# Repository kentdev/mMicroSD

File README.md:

mMicroSD
========

Source code and EAGLE schematic for the mMicroSD peripheral for the M2 (http://medesign.seas.upenn.edu/index.php/Guides/MaEvArM), which allows it to read from and write to a microSD card.

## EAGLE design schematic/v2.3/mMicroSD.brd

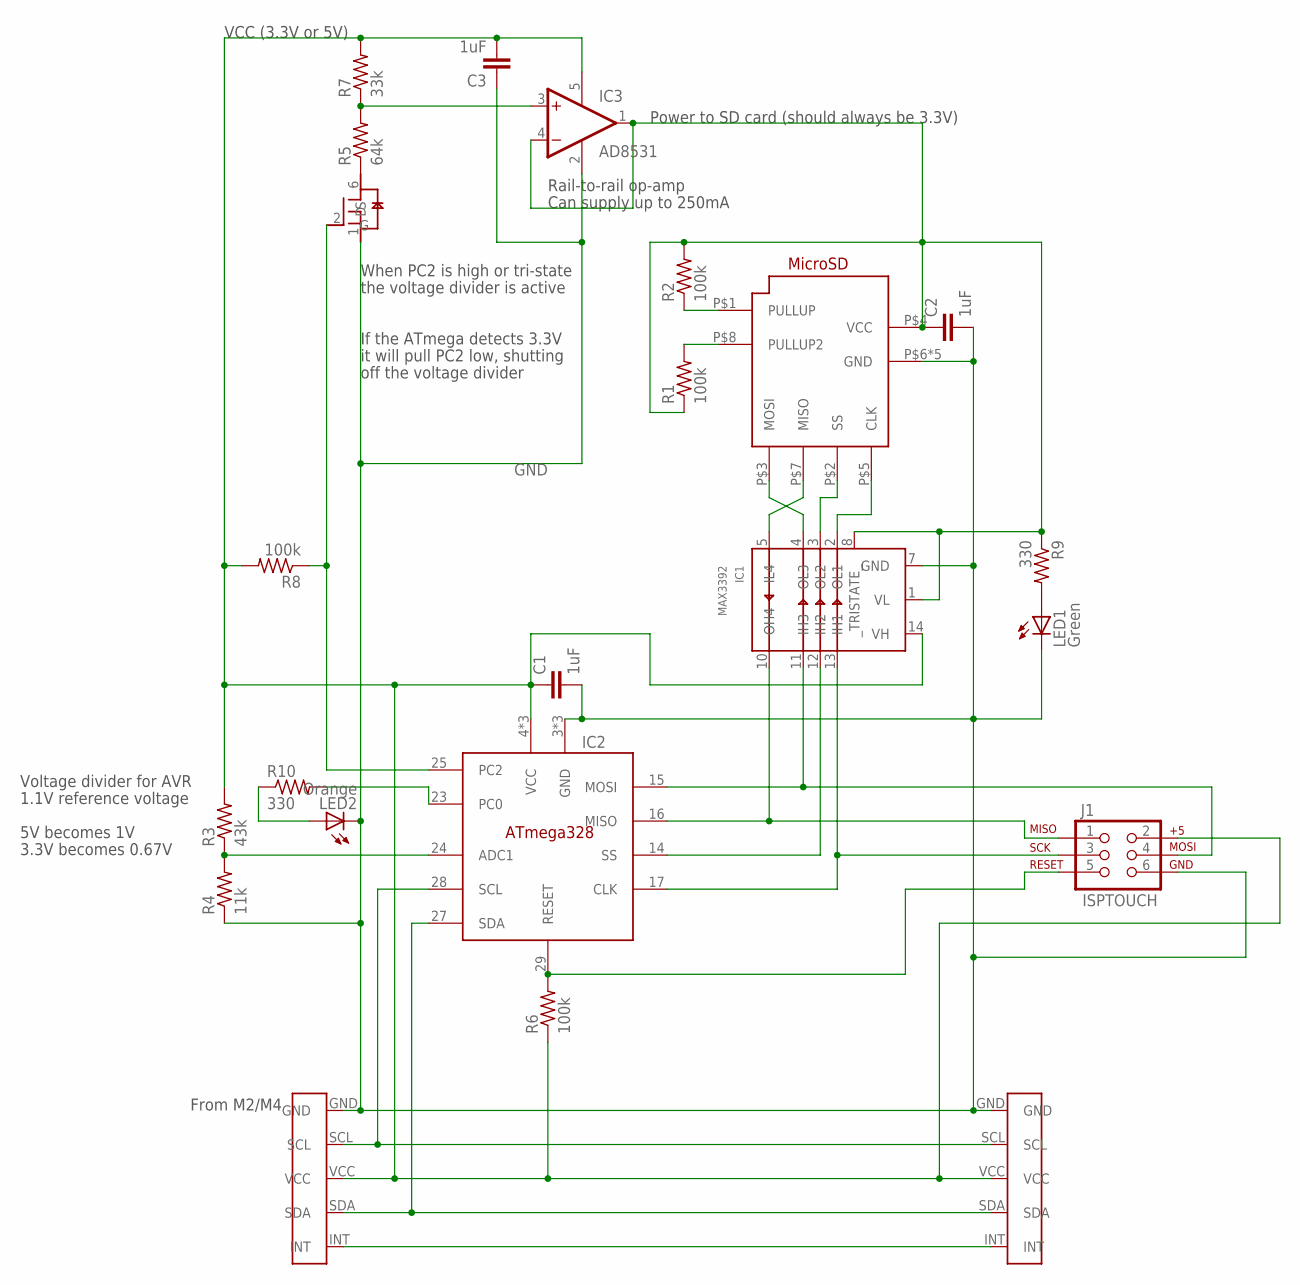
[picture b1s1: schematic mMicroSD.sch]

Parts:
C1, C2, C3: 1uF; C0603
IC1: MAX3392; 14-TSSOP
IC2: ATMEGA328
IC3: AD8531; SOT-23-5
J1: ISPTOUCH; AVX_9188_6-WAY_SMT
LED1: Green; SML0603
LED2: Orange; SML0603
M1: NTJD5121N; SOT-363
R1, R2, R6, R8: 100k; R0603
R3: 43k; R0603
R4: 11k; R0603
R5: 64k; R0603
R7: 33k; R0603
R9, R10: 330; R0603
SDCONN: 101-00660-68-6
U$1: MBUS_OUT
U$2: MBUS_IN

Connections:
ADC_LINE: IC2.24 (ADC1), R3.1, R4.2
DATA_LED: IC2.23 (PC0), R10.2
GATE: IC2.25 (PC2), M1.2 (G), R8.1
GND: C1.2, C2.2, C3.1, IC1.7 (GND), IC2.3 (GND), IC2.5 (GND), IC2.21 (GND), IC3.2 (V-), J1.6, LED1.C, LED2.C, M1.1 (S), R4.1, SDCONN.P$6 (GND), SDCONN.P$9 (GND), SDCONN.P$10 (GND), SDCONN.P$11 (GND), SDCONN.P$12 (GND), U$1.GND, U$2.GND
INT: U$1.INT, U$2.INT
MISO: IC1.10 (OH4), IC2.16 (MISO), J1.1
MOSI: IC1.11 (IH3), IC2.15 (MOSI), J1.4
unnamed: M1.6 (D), R5.1
unnamed: LED1.A, R9.2
unnamed: LED2.A, R10.1
unnamed: R1.2, SDCONN.P$8 (PULLUP2)
unnamed: R2.1, SDCONN.P$1 (PULLUP)
OPAMP_VOLTAGE: IC3.3 (+IN), R5.2, R7.1
RESET: IC2.29 (RESET), J1.5, R6.2
SCK: IC1.13 (IH1), IC2.17 (CLK), J1.3
SCL: IC2.28 (SCL), U$1.SCL, U$2.SCL
SDA: IC2.27 (SDA), U$1.SDA, U$2.SDA
SD_CS: IC1.3 (OL2), SDCONN.P$2 (SS)
SD_MISO: IC1.5 (IL4), SDCONN.P$7 (MISO)
SD_MOSI: IC1.4 (OL3), SDCONN.P$3 (MOSI)
SD_SCK: IC1.2 (OL1), SDCONN.P$5 (CLK)
SS: IC1.12 (IH2), IC2.14 (SS)
VCC_MBUS: C1.1, C3.2, IC1.14 (VH), IC2.4 (VCC), IC2.6 (VCC), IC2.18 (VCC), IC3.5 (V+), J1.2, R3.2, R6.1, R7.2, R8.2, U$1.VCC, U$2.VCC
VCC_SD: C2.1, IC1.1 (VL), IC1.8 (_TRISTATE_), IC3.1 (OUT), IC3.4 (-IN), R1.1, R2.2, R9.1, SDCONN.P$4 (VCC)

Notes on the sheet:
From M2/M4
VCC (3.3V or 5V)
Voltage divider for AVR
1.1V reference voltage
5V becomes 1V
3.3V becomes 0.67V
When PC2 is high or tri-state
the voltage divider is active
If the ATmega detects 3.3V
it will pull PC2 low, shutting
off the voltage divider
Power to SD card (should always be 3.3V)
Rail-to-rail op-amp
Can supply up to 250mA

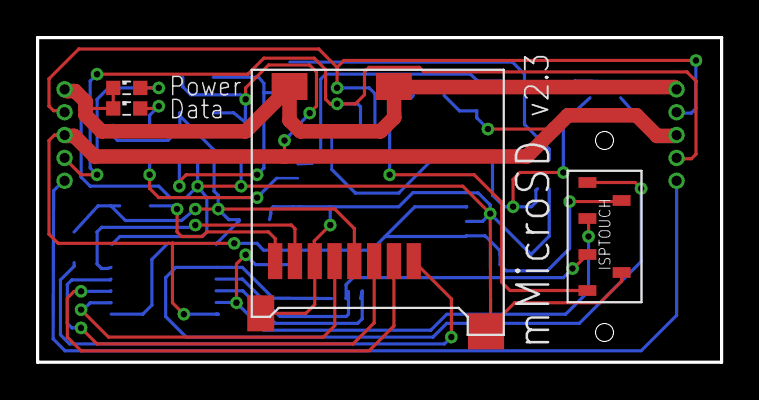
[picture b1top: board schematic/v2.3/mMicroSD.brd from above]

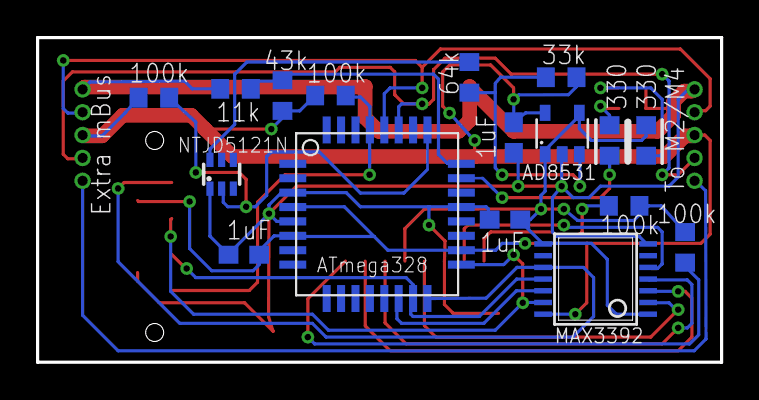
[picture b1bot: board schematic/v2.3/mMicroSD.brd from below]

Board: 2 copper layers, 38.0 x 18.0 mm, 23 parts (17 on the bottom side), 24 nets.

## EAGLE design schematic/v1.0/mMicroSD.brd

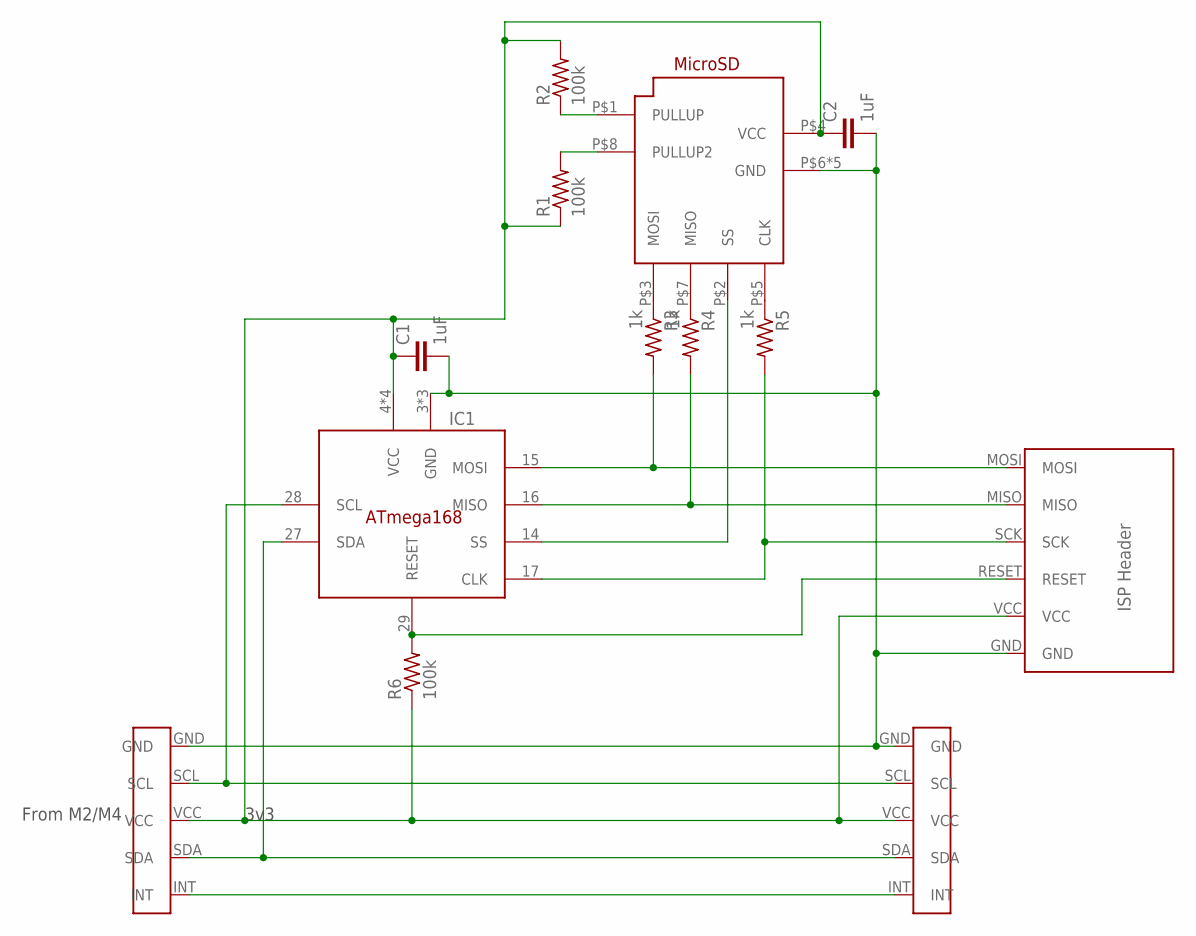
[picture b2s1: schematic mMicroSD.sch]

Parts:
C1, C2: 1uF; C0805
IC1: ATMEGA168
R1, R2, R6: 100k; R2012
R3, R4, R5: 1k; R2012
SDCONN: 101-00660-68-6
U$1: MBUS_OUT
U$2: MBUS_IN
U$3: ISP

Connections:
GND: C1.2, C2.2, IC1.3 (GND), IC1.5 (GND), IC1.21 (GND), SDCONN.P$6 (GND), SDCONN.P$9 (GND), SDCONN.P$10 (GND), SDCONN.P$11 (GND), SDCONN.P$12 (GND), U$1.GND, U$2.GND, U$3.GND
unnamed: U$1.INT, U$2.INT
unnamed: IC1.27 (SDA), U$1.SDA, U$2.SDA
unnamed: IC1.28 (SCL), U$1.SCL, U$2.SCL
unnamed: IC1.14 (SS), SDCONN.P$2 (SS)
unnamed: R3.1, SDCONN.P$3 (MOSI)
unnamed: R4.1, SDCONN.P$7 (MISO)
unnamed: IC1.16 (MISO), R4.2, U$3.MISO
unnamed: IC1.15 (MOSI), R3.2, U$3.MOSI
unnamed: IC1.29 (RESET), R6.2, U$3.RESET
unnamed: R1.2, SDCONN.P$8 (PULLUP2)
unnamed: R2.1, SDCONN.P$1 (PULLUP)
unnamed: IC1.17 (CLK), R5.2, U$3.SCK
unnamed: R5.1, SDCONN.P$5 (CLK)
VCC: C1.1, C2.1, IC1.4 (VCC), IC1.6 (VCC), IC1.18 (VCC), IC1.20 (VCC), R1.1, R2.2, R6.1, SDCONN.P$4 (VCC), U$1.VCC, U$2.VCC, U$3.VCC

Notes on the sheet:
3v3
From M2/M4

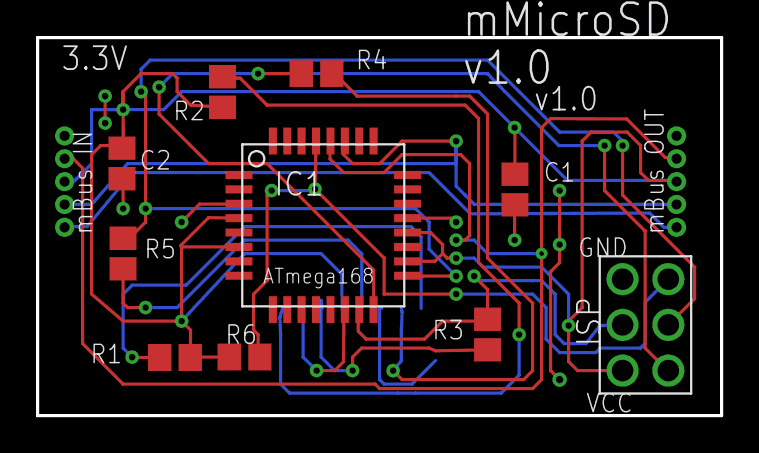
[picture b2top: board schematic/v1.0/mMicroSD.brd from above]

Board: 2 copper layers, 38.0 x 21.0 mm, 13 parts (1 on the bottom side), 15 nets.

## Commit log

2014-10-27 Removed text editor temp files
2014-10-27 Changed symlinks to have relative paths
2014-12-19 Fixed length issues in filesystem characters vs normal file names
2014-12-19 Moved common functionality (mBus commands and FAT32-name-on-filesystem <-> regular-8.3-filename conversion code) into a common directory
2014-12-19 Updated the M2 direct microSD code to use the common FS name conversion code, and copied the test code from m2_mbus
2014-12-19 Added common FAT32 name conversion code to the direct M4 code
2014-12-25 Added a command to commit pending writes to the microSD card
2014-12-28 Renamed the mMicroSD directory to 'code', so now we have 'code' and 'schematic' instead of 'mMicroSD' and 'schematic'
2014-12-28 Added a new version of the mMicroSD board, now with programming pin guides that won't collide with the microSD card holder
2015-02-01 Added EAGLE temporary files to .gitignore
2015-02-02 Created new mMicroSD board layout, to give enough space for the ISPtouch programming adapter and to reduce the board size to match the M2 and M4 widths
2015-02-02 Moved a few value labels around for better readability
2015-02-19 Moved cap label a bit
2015-03-01 Added some silkscreen to the board to make the orientation of two close resistors more apparent
2015-03-01 Another small silkscreen change
2015-03-03 Fixed a couple traces that had been disconnected accidentally while debugging
2015-04-04 Fixed a bug in finding the first FAT32 sector (the number of hidden sectors doesn't matter
2015-04-04 Added fuses to the makefile
2015-04-04 Moved more commonly-used code files to the common directory
2015-04-16 Made a wrapper around the debugging code and moved more files into the common area
2015-04-16 Updated makefiles to include the debug code
2015-04-18 Updated debugging for the FAT32 filesystem code
2015-04-18 Added gedit temporary files (*~) to the ignore list
2015-05-24 Created new (WIP) version of the board, with a pull-up resistor on the SD card's MISO line
2015-05-24 Gave names to some previously anonymous lines
2015-05-28 Updated debug code to initialize the debugging interface the first time a debug function is called
